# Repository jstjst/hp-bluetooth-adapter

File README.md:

# hp-bluetooth-adapter

Datasheet of the Bluetooth-Modul: https://www.pollin.de/productdownloads/D722335D.PDF

Pololu 5V Step-Up Voltage Regulator U1V10F5: https://www.pololu.com/product/2564

  https://www.ebay.de/itm/Pololu-5V-Step-Up-Spannungsregler-U1V10F5-2564/272202544751
  
Connector JST SM06B-XSRS-ETB: http://www.jst-mfg.com/product/detail_e.php?series=466

  http://www.jst-mfg.com/product/pdf/eng/eXSR.pdf

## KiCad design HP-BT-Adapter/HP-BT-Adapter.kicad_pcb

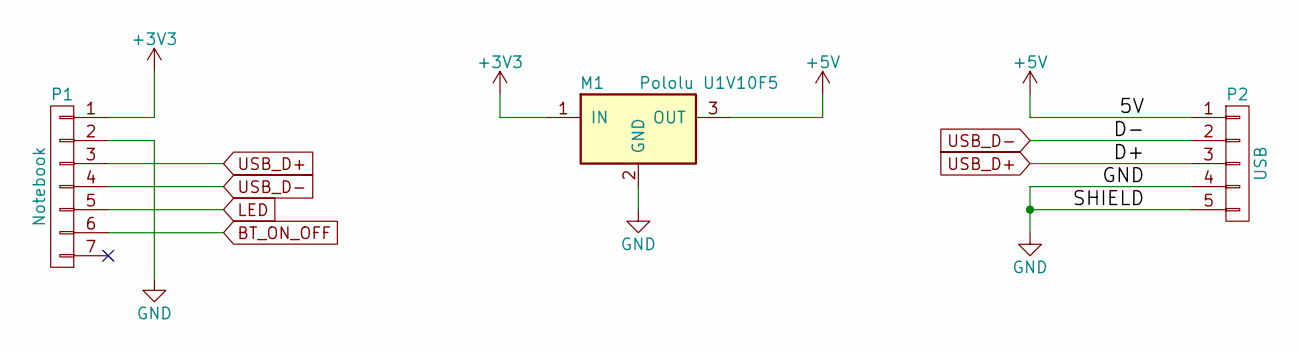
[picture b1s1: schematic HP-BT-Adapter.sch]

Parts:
M1: Pololu U1V10F5; Pololu_U1V10F5
P1: Notebook; JST_SM06B-XSRS-ETB
P2: USB; USB_A

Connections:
+3V3: M1.1 (IN), P1.1
+5V: M1.3 (OUT), P2.1
BT_ON_OFF: P1.6
GND: M1.2 (GND), P1.2, P2.4, P2.5
LED: P1.5
USB_D+: P1.3, P2.3
USB_D-: P1.4, P2.2

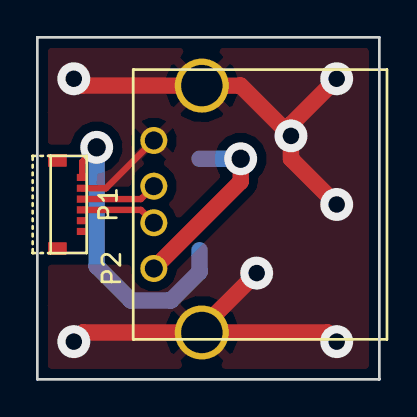
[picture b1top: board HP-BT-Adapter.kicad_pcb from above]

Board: 2 copper layers, 19.0 x 19.0 mm, 3 parts (1 on the bottom side), 5 nets.

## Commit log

2017-11-25 datasheet of the BT Modul
2017-11-27 schematic and layout
2017-11-27 Finished v1.0
